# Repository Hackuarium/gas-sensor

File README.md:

# gas-sensor

The goal is to create a box allowing the determination of the gas composition of a bioreactor. The sensor that will be available are: CO2 (MH-Z19), H2 (MQ-8) and methane (MQ-4) as well as temperature (DS18B20) and humidity (DHT-22).

The board will be compatible with arduino Lilapad Pro using a dedicated PCB.

Need to compensate for humidity and temperature ???

- https://forum.arduino.cc/index.php?topic=433045.0

## Cloning the project

This project uses SUBMODULES

In order to clone use:

`git clone --recurse-submodules https://github.com/hackuarium/gas-sensor`

To update the submodules

`git submodule update --recursive --remote`

## Sensors

| name_pin | function    | model   |                             | Arduino library                                |
| -------- | ----------- | ------- | --------------------------- | ---------------------------------------------- |
| CH4      | CH4         | MQ-4    |                             |                                                |
| H2       | H2          | MQ-8    |                             |                                                |
| CO2      | CO2         | MH-Z19  | 3.3v (for RX / TX) + 5v!!!! | https://github.com/crisap94/MHZ19              |
| TEMP     | temperature | DS18B20 |                             |                                                |
| HUM      | humidity    | DHT-22  |                             | https://github.com/adafruit/DHT-sensor-library |

Gaz sensor: http://www.china-total.com/Product/meter/gas-sensor/Gas-sensor.htm

Gaz sensor on sparkfun:
https://www.sparkfun.com/products/8891
https://www.sparkfun.com/products/9404

Gaz sensor on mysensors: https://www.mysensors.org/build/gas

Drying the air / pumping
Particulate or Coalescing Filters
http://www.pneumaticplus.com/pneumaticplus-saf4000-series-particulate-air-filter-1-2-npt-with-bracket/
https://www.aliexpress.com/item/15L-M-12V-dc-electric-diaphragm-brush-small-air-compressor-pump/1790013118.html

Fans

https://www.pelonistechnologies.com/micro-fans

Pneumatic
https://www.alibaba.com/product-detail/A102-China-sup

## Pinout

| n° Arduino | port | pin      |                  |     |
| ---------- | ---- | -------- | ---------------- | --- |
| A0         | PC0  | A0       | H2               |     |
| A1         | PC1  | A1       | H2_ON            |     |
| A2         | PC2  | A2       | CO2_RX           |     |
| A3         | PC3  | A3       | CO2_TX           |     |
| A4         | PC4  | SDA      | Slave I2C        |     |
| A5         | PC5  | SCL      | Slave I2C        |     |
| A6         | ADC6 | A6       | CH4              |     |
| A7         | ADC7 | A7       | CH4_ON           |     |
| 0          | PD0  | RX       | FTDI             |     |
| 1          | PD1  | TX       | FTDI             |     |
| 2          | PD2  | D2       | /                |     |
| 3          | PD3  | D3       | PWM_MH-Z19       | PWM |
| 4          | PD4  | D4       | TEMPERATURE      |     |
| 5          | PD5  | D5       | HUMIDITY         | PWM |
| 6          | PD6  | D6       | LCD RS           | PWM |
| 7          | PD7  | D7       | /                |     |
| 8          | PB0  | D8       | LCD E            |     |
| 9          | PB1  | D9       | LCD LED          | PWM |
| 10         | PB2  | D10      | LCD1             | PWM |
| 11         | PB3  | MOSI D11 | LCD2             | PWM | mh |
| 12         | PB4  | MISO D12 | LCD3             |     |
| 13         | PB5  | SCK D13  | LCD4             |     |

n.b: Two pins (PD2 and PD7) are free and could be used to add a fourth sensor.

## Power supply

- plug for 5V
- MCP1703-33 for µC power supply

## Schematic
Here is the schematic of the main components of the project:

ATMega328P:

Sensors:

Others (LCD, crystal and voltage regulator):

## List of components
| Type           | Value | Quantity | Footprint                   |
|----------------|-------|----------|-----------------------------|
| Resistor       | 1M    | 1        | 0805 Handsolder             |
| Resistor       | 10k   | 2        | 0805 Handsolder             |
| Resistor       | 4.7k  | 2        | 0805 Handsolder             |
| Resistor       | 4.7   | 1        | 0805 Handsolder             |
| Potentiometer  |       | 1        | TRIM_3362R-1-222            |
| Capacitor      | 10µF  | 2        | 0805 Handsolder             |
| Capacitor      | 100nF | 3        | 0805 Handsolder             |
| Capacitor      | 18pF  | 2        | 0805 Handsolder             |
| Diode Shottky  |       | 3        | D_SOD-123                   |
| BSP75          |       | 2        | SOT-223-3_TabPin3           |
| Crystal        | 8Mhz  | 1        | Crystal_SMD_5032 Handsolder |
| MCP-1703A      |       | 1        | SOT-23                      |
| ATMega328P-AU  |       | 1        | TQFP-32_7x7mm_P0.8mm        |
| 5V power source|       | 1        | BarrelJack_Horizontal       |
| RJ12           |       | 1        | RJ12_Amphenol_54601         |
| LCD Screen     |       | 1        | WC1602A                     |
| MHZ-19 (CO2)   |       | 1        | footprints: MHZ-19          |
| MQ-4 (CH4)     |       | 1        | footprints: MQ-4            |
| MQ-8 (H2)      |       | 1        | footprints: MQ-8            |
| DHT22 (Hum)    |       | 1        | footprints: DHT-22_HOR      |
| DS18B20 (Temp) |       | 1        | TO-92_Inline                |

## Inspiration for PCB

* https://github.com/Hackuarium/esp-12e/tree/master/kicad

  - ICSP - TAG connect - take care of pin mapping !
  - RJ12 - 6P6C
  - FTDI232
  - LCD: WC1602A

## Get inspired from scale board

- https://github.com/Hackuarium/beemos/tree/master/scale-i2c/eagle
- https://github.com/Hackuarium/esp-12e/tree/master/kicad/libs

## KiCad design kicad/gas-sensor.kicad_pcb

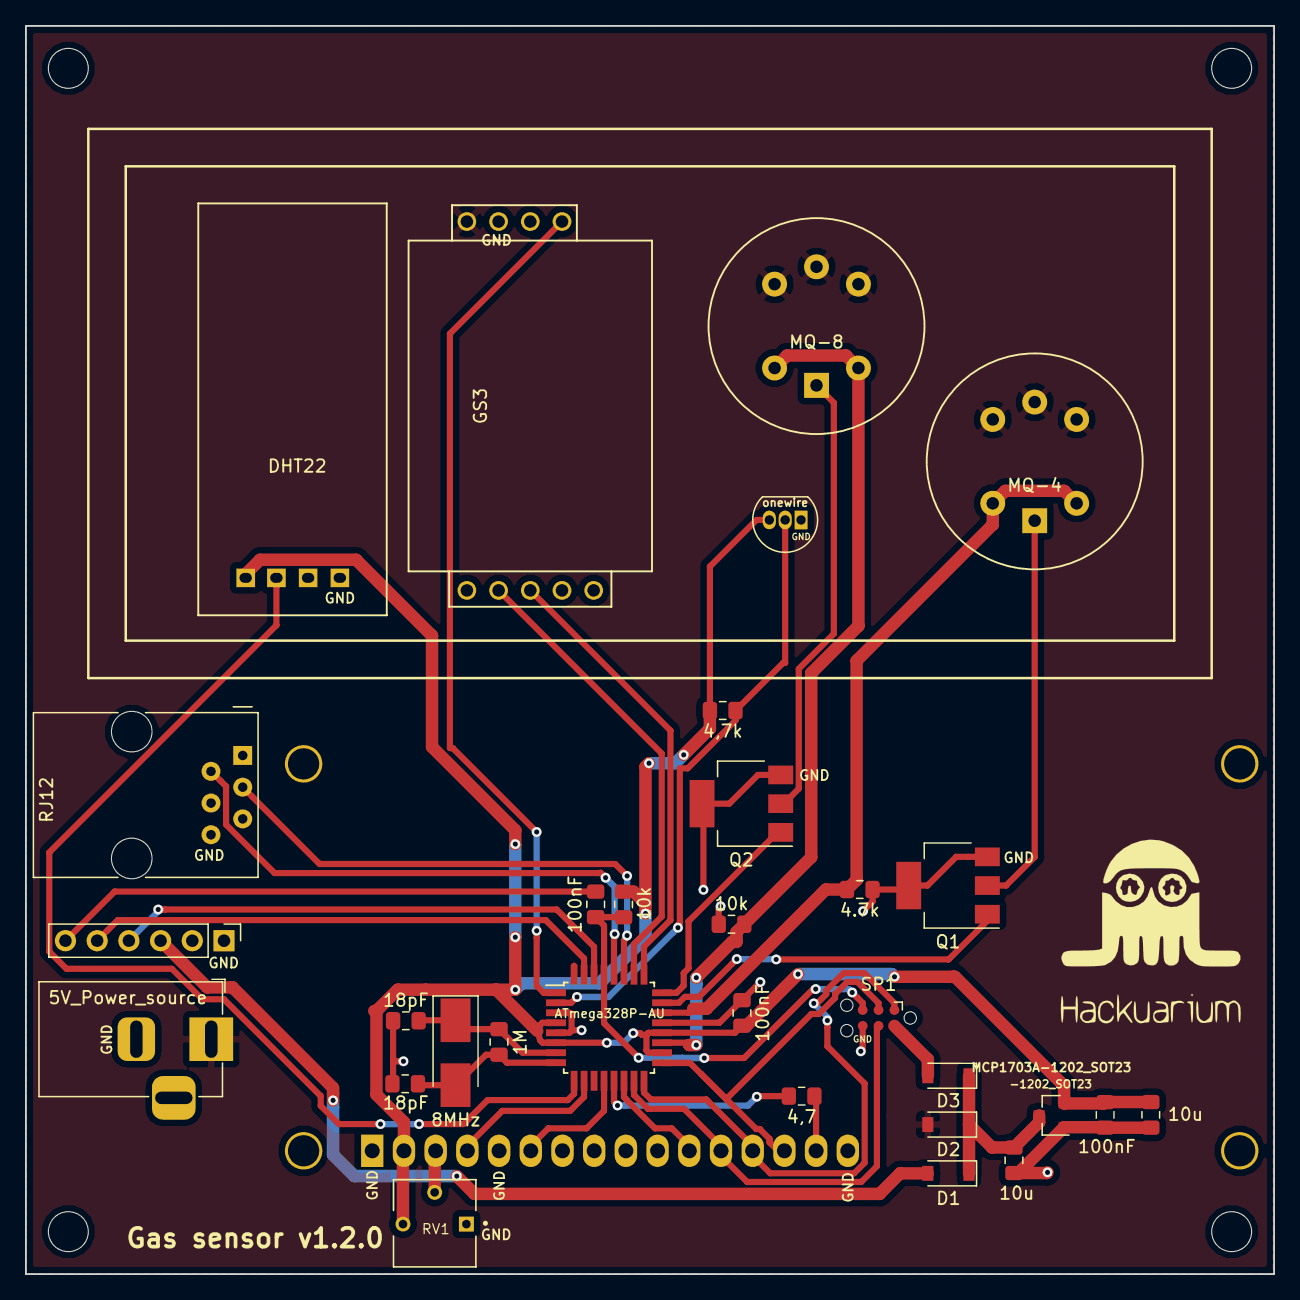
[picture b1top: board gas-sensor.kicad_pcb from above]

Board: 2 copper layers, 100.0 x 100.0 mm, 37 parts (1 on the bottom side), 34 nets.

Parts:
C1, C2: 18pF; C_0805_2012Metric_Pad1.15x1.40mm_HandSolder
C3, C7: 10u; C_0805_2012Metric_Pad1.15x1.40mm_HandSolder
C4, C5, C6: 100nF; C_0805_2012Metric_Pad1.15x1.40mm_HandSolder
D1, D2, D3: D_Schottky; D_SOD-123
DS1: WC1602A
G1: LOGO; hackuarium
GS1: MQ-4
GS2: MQ-8
GS3: MH-Z19
J1: Conn FT232RL; PinHeader_1x06_P2.54mm_Vertical
J2: RJ12; RJ12_Amphenol_54601
J3, J4, J5, J6: hole; MountingHole_3.2mm_M3
J7: 5V_Power_source; BarrelJack_Horizontal
Q1, Q2: BSP75; SOT-223-3_TabPin3
R1: 1M; R_0805_2012Metric_Pad1.15x1.40mm_HandSolder
R2: 4,7; R_0805_2012Metric_Pad1.15x1.40mm_HandSolder
R3, R5: 10k; R_0805_2012Metric_Pad1.15x1.40mm_HandSolder
R4: 4.7k; R_0805_2012Metric_Pad1.15x1.40mm_HandSolder
R6: 4,7k; R_0805_2012Metric_Pad1.15x1.40mm_HandSolder
RV1: R_POT; TRIM_3362R-1-222
SP1: ICSP; Tag-Connect_TC2030-IDC-NL_2x03_P1.27mm_Vertical
U1: DS18B20; TO-92_Inline
U2: ATmega328P-AU; TQFP-32_7x7mm_P0.8mm
U3: DHT22; DHT22_HOR
U4: MCP1703A-1202_SOT23; SOT-23
Y1: 8MHz; Crystal_SMD_5032-2Pin_5.0x3.2mm_HandSoldering

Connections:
+5V: D2.2, GS1.3, GS1.4, GS1.5, GS2.3, GS2.4, GS2.5, GS3.6, J7.1
/DTR: C6.1, J1.6
/HUM: U2.9, U3.2
/LCD1: DS1.11, U2.14
/LCD2_MOSI: DS1.12, SP1.4, U2.15
/LCD3_MISO: DS1.13, SP1.1, U2.16
/LCD4_SCK: DS1.14, SP1.3, U2.17
/LCD_E: DS1.6, U2.12
/LCD_LED: R2.1, U2.13
/LCD_RS: DS1.4, U2.10
/PWM_MH-Z19: GS3.9, U2.1
/RESET: C6.2, R3.2, SP1.5, U2.29
/RX: J1.4, U2.30
/RX_MH-Z19: GS3.3, U2.25
/SCL: J2.2, U2.28
/SDA: J2.3, U2.27
/Sensor1: GS1.1, GS1.2, R4.1, U2.22
/Sensor1_ON: Q1.1, U2.23
/Sensor2: GS2.1, GS2.2, R5.1, U2.19
/Sensor2_ON: Q2.1, U2.24
/TEMP: R6.2, U1.2, U2.2
/TX: J1.5, U2.31
/TX_MH-Z19: GS3.2, U2.26
/VCC-FTDI: D1.2, J1.3
/VCC-ICSP: D3.2, SP1.2
/XTAL1: C1.1, R1.1, U2.7, Y1.1
/XTAL2: C2.1, R1.2, U2.8, Y1.2
GND: C1.2, C2.2, C3.2, C4.2, C5.2, C7.2, DS1.1, DS1.5, DS1.16, GS3.7, J1.1, J2.4, J2.6, J7.2, Q1.3, Q2.3, R4.2, R5.2, RV1.1, SP1.6, U1.1, U2.3, U2.5, U2.21, U3.4, U4.1
unnamed: C7.1, D1.1, D2.1, D3.1, U4.3
unnamed: DS1.3, RV1.2
unnamed: DS1.15, R2.2
unnamed: GS1.6, Q1.2
unnamed: GS2.6, Q2.2
VCC: C3.1, C4.1, C5.1, DS1.2, R3.1, R6.1, RV1.3, U1.3, U2.4, U2.6, U2.18, U2.20, U3.1, U4.2

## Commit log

2018-12-04 add specdtro
2019-02-05 description of new project
2019-02-05 add pwm information
2019-02-05 update CO2 gas sensor and reset
2019-02-05 add link to gas sensor
2019-02-05 add remarks about temperature
2019-02-13 Add Olivier file
    First draft of shematic
2019-02-21 add more info in readme
2019-02-26 Footprints and first PCB draft
    add kicad (+libs) and docs file, sorted libs, footprints of sensors, first draft of PCB
2019-02-26 minor changes
2019-03-05 First version of PCB
    with 3D components
2019-03-07 Update README.md
    change PIN configuration
2019-03-13 Update
    With space for plexiglas box
2019-03-14 add gerber files and version
2019-03-14 update pcb and submit gerber
2019-03-22 Update after debugging
2019-03-25 gerver v1.1.0
2019-03-26 add missing dri files in gerber.110
2019-04-01 add first multithread program
2019-04-02 improve code
2019-04-08 Rx/Tx + Potentiometer ok
2019-04-10 Update
    Plans for laser cut (simple & with clips)
2019-04-10 Delete eagle file
    Unused and useless
2019-04-10 Added voltage regulator
2019-04-22 Update CAD
2019-04-30 Update PCB
    ready for GERBER
2019-05-17 Final version of box
2019-05-17 Add images schématic
2019-05-24 Update Code
